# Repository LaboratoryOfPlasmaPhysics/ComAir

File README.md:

# ComAir

A LoRa air quality sensor powered with an indoor solar pannel.

This PCB uses:
- as MCU: [STM32L412C8](https://www.st.com/en/microcontrollers-microprocessors/stm32l412c8.html)
- for LoRa communication: [RFM95](https://www.hoperf.com/modules/lora/RFM95.html)
- for energy harvesting: [SPV1050](https://www.st.com/en/power-management/spv1050.html)
- any 18650 lithium cell (could be recycled from old laptop battery)
- as solar pannel, one or two: [LL200-4.8-37](https://www.powerfilmsolar.com/products/electronic-component-solar-panels/indoor-light-series/ll200-48-37) 
- for CO2 sensing: [SCD41](https://www.sensirion.com/en/environmental-sensors/carbon-dioxide-sensors/carbon-dioxide-sensor-scd4x/)
- for temperature and humidity: either [SCD41](https://www.sensirion.com/en/environmental-sensors/carbon-dioxide-sensors/carbon-dioxide-sensor-scd4x/) or [SHTC3](https://www.sensirion.com/en/environmental-sensors/humidity-sensors/digital-humidity-sensor-shtc3-our-new-standard-for-consumer-electronics/)

**Warning** this project is still work in progress, PCB may still contain errors.

PCB V1.0 preview:

## TODO

- [ ] Write some basic testing firmware
- [ ] Evaluate energy balance 
- [ ] Optimize energy usage

## License 
- CC-BY-SA

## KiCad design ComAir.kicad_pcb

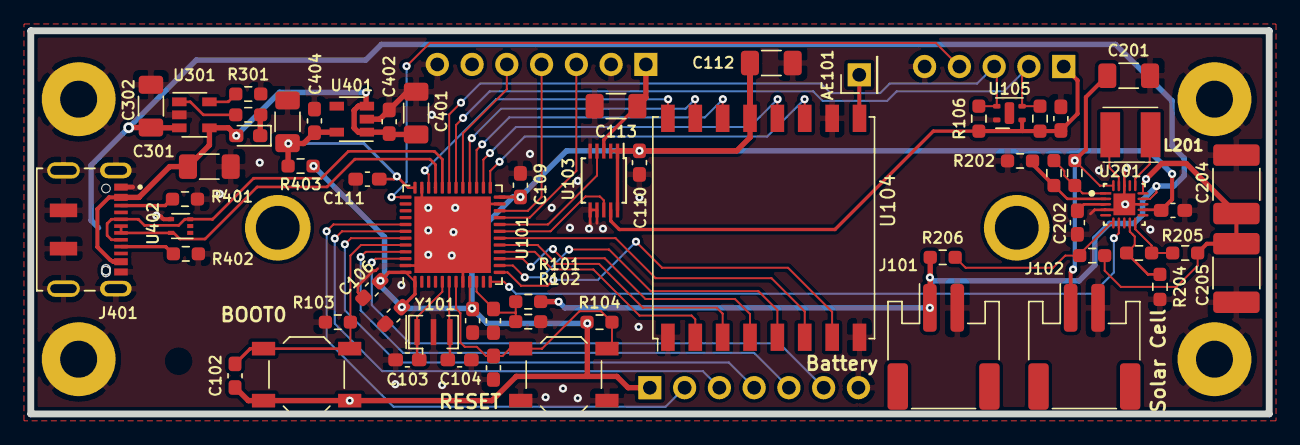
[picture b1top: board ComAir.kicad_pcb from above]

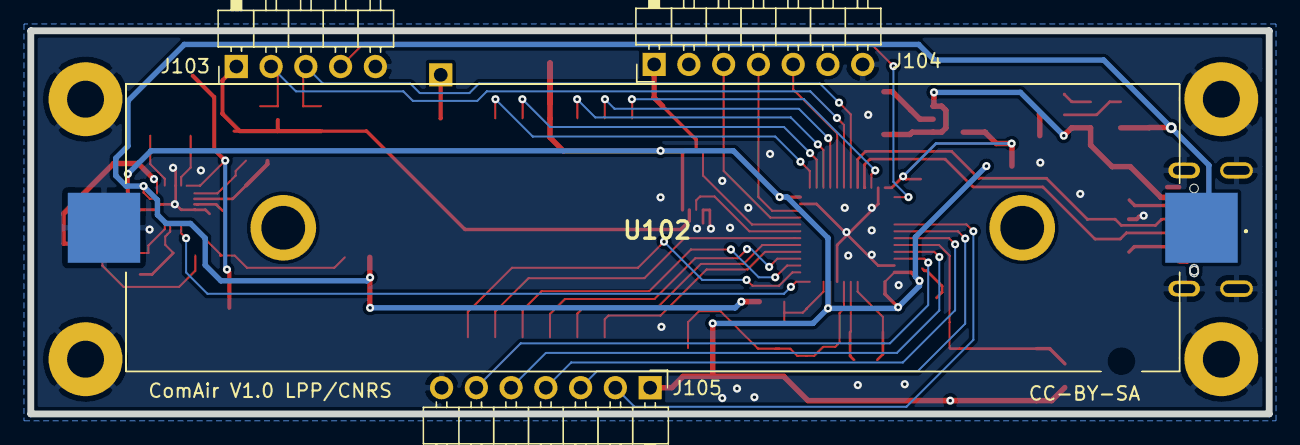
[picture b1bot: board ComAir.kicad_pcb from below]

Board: 2 copper layers, 90.5 x 28.0 mm, 69 parts (4 on the bottom side), 55 nets.

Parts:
AE101: Antenna; PinHeader_1x01_P2.54mm_Vertical
C101, C102, C105, C106, C107, C108, C109, C110, C111, C114, C202, C203, C402, C404: 100nF; C_0603_1608Metric_Pad1.08x0.95mm_HandSolder
C103, C104: 20pF; C_0603_1608Metric_Pad1.08x0.95mm_HandSolder
C112, C113: 10uF; C_1206_3216Metric_Pad1.33x1.80mm_HandSolder
C201: 1uF; C_1206_3216Metric_Pad1.33x1.80mm_HandSolder
C204, C205: 47uF; C_1812_4532Metric_Pad1.57x3.40mm_HandSolder
C301, C302, C401, C403: 4.7uF; C_1206_3216Metric_Pad1.33x1.80mm_HandSolder
D301: LED; LED_0603_1608Metric_Pad1.05x0.95mm_HandSolder
H101, H102, H103, H104: MountingHole_Pad; MountingHole_2.7mm_M2.5_Pad
J101, J102: Conn_01x02; JST_PH_S2B-PH-SM4-TB_1x02-1MP_P2.00mm_Horizontal
J103: Conn_01x05; PinHeader_1x05_P2.54mm_Horizontal
J104, J105: Conn_01x07; PinHeader_1x07_P2.54mm_Horizontal
J401: DX07S016JA1R1500; JAE_DX07S016JA1R1500
L201: L; LQH44PH100MPRL
R101: 1M; R_0603_1608Metric_Pad0.98x0.95mm_HandSolder
R102: 2M; R_0603_1608Metric_Pad0.98x0.95mm_HandSolder
R103, R104: 10k; R_0603_1608Metric_Pad0.98x0.95mm_HandSolder
R105, R106: 4k7; R_0603_1608Metric_Pad0.98x0.95mm_HandSolder
R201, R202, R203, R204, R205, R206, R207, R208: R; R_0603_1608Metric_Pad0.98x0.95mm_HandSolder
R301: 2k; R_0603_1608Metric_Pad0.98x0.95mm_HandSolder
R302: 470; R_0603_1608Metric_Pad0.98x0.95mm_HandSolder
R401, R402: 5.1k; R_0603_1608Metric_Pad0.98x0.95mm_HandSolder
R403: 0; R_0603_1608Metric_Pad0.98x0.95mm_HandSolder
SW101, SW102: SW_Push; SW_SPST_TL3342
U101: STM32L431CBUx; QFN-48-1EP_7x7mm_P0.5mm_EP5.6x5.6mm
U102: 12BHC186P1-GR; 12BHC186P1GR
U103: TS3A24159DGSR; TSSOP-10_3x3mm_P0.5mm
U104: RFM95W-868S2; HOPERF_RFM9XW_SMD
U105: SHTC3; Sensirion_DFN-4-1EP_2x2mm_P1mm_EP0.7x1.6mm
U201: SPV1050TTR; STMicroelectronics-SPV1050TTR-0
U301: MCP73831-2-OT; SOT-23-5
U401: NCP718xSN330; SOT-23-5
U402: TPD2E2U06; SOT-553
Y101: Crystal_GND2_Small; Resonator_SMD_muRata_CSTxExxV-3Pin_3.0x1.1mm

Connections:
/3V3: C102.1, C105.1, C106.1, C108.1, C109.1, C110.1, C112.1, C203.1, J105.1, R104.1, R403.2, SW101.1, U101.1, U101.9, U101.24, U101.48, U103.1, U103.2, U103.10, U104.13, U201.12
/3V3_SCD30: C113.1, J104.1, U103.3
/BOOT0: C102.2, R103.1, SW101.2, U101.44
/I2C1_SCL: J103.2, R105.2, U101.30, U105.2
/I2C1_SDA: J103.3, R106.2, U101.31, U105.3
/I2C2_SCL: J104.3, U101.21
/I2C2_SDA: J104.4, U101.22
/LORA_DIO0: U101.27, U104.14
/LORA_DIO1: U101.28, U104.15
/LORA_DIO2: U101.34, U104.16
/LORA_DIO3: U101.25, U104.11
/LORA_DIO4: U101.26, U104.12
/LORA_DIO5: U101.13, U104.7
/LORA_RESET: U101.18, U104.6
/LP_SENSORS_3V3: C114.1, J103.1, R105.1, R106.1, U103.9, U105.1
/LP_SENSORS_PW_EN: U101.19, U103.8
/OneWire: J103.4, U101.37
/PB5: J105.2, U101.41
/PB6: J105.3, U101.42
/PB7: J105.4, U101.43
/PB8: J105.5, U101.45
/PB9: J105.6, U101.46
/Power_Harvester/Store: C204.1, C205.1, R205.1, R207.1, U201.15
/SCD30_PW_EN: U101.20, U103.4
/SCD30_RDY: J104.5, U101.29
/SPI1_MISO: U101.16, U104.2
/SPI1_MOSI: U101.17, U104.3
/SPI1_NSS: U101.14, U104.5
/SPI1_SCK: U101.15, U104.4
/SolarCell: C201.1, J102.1, R201.1, U201.20
/USB_D+: J401.6, J401.7, U101.33, U402.5
/USB_D-: J401.5, J401.8, U101.32, U402.3
/USB_VBUS: C301.1, C401.1, C402.1, D301.2, J401.2, J401.11, U301.4, U401.1, U401.3
/VBAT_Sense: C101.1, R101.2, R102.1, U101.10
/VBat: C302.1, J101.1, R101.1, R206.1, U102.1, U201.14, U301.3
/VDD_USB: C111.1, C403.1, C404.1, R403.1, U101.36, U401.5
/~BATT_CHRG: U101.12, U201.7
/~RESET: C107.1, R104.2, SW102.1, U101.7
GND: C101.2, C103.2, C104.2, C105.2, C106.2, C107.2, C108.2, C109.2, C110.2, C111.2, C112.2, C113.2, C114.2, C201.2, C202.2, C203.2, C204.2, C205.2, C301.2, C302.2, C401.2, C402.2, C403.2, C404.2, H101.1, H102.1, H103.1, H104.1, J101.2, J102.2, J103.5, J104.2, J104.7, J105.7, J401.1, J401.12, J401.S1, J401.S2, J401.S3, J401.S4, J401.S5, J401.S6, R102.2, R103.2, R202.1, R204.1, R301.2, R401.1, R402.1, SW102.2, U101.8, U101.23, U101.35, U101.47, U101.49, U102.2, U103.5, U103.6, U103.7, U104.1, U104.8, U104.10, U105.4, U201.4, U201.13, U201.18, U201.21, U301.2, U401.2, U402.4, Y101.2
unnamed: AE101.1, U104.9
unnamed: C103.1, U101.5, Y101.1
unnamed: C104.1, U101.6, Y101.3
unnamed: C202.1, U201.3
unnamed: D301.1, R302.1
unnamed: J401.3, R401.2
unnamed: J401.9, R402.2
unnamed: L201.1, U201.19
unnamed: L201.2, U201.16
unnamed: R201.2, R203.1, U201.1
unnamed: R202.2, R203.2, U201.2
unnamed: R204.2, R208.1, U201.9
unnamed: R205.2, R208.2, U201.10
unnamed: R206.2, R207.2, U201.6
unnamed: R301.1, U301.5
unnamed: R302.2, U301.1

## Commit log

2021-05-12 initial release
2021-05-24 PCB ready for first prototype production
2021-06-12 Adds readme with a picture
